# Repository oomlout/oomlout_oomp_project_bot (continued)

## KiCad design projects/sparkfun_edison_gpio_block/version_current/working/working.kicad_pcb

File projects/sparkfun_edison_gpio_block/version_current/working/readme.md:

# Edison_GPIO_Block by sparkfun  
This is a harvested standardized copy of a project from github.  
The original project can be found at:  
https://github.com/sparkfun/Edison_GPIO_Block  
Please consult that link for additional, details, files, and license information.  
Note: It was auto harvested and if the original repo had more than one board file or anything out of the ordinary the files here are likely not representative.

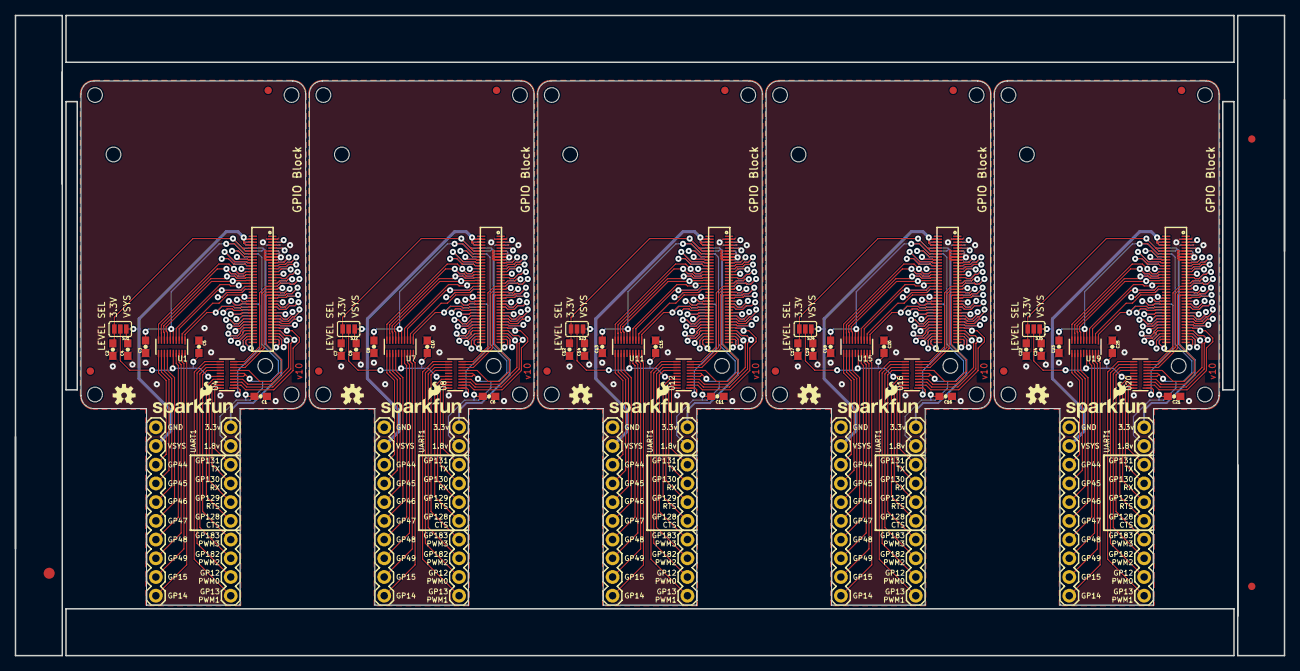
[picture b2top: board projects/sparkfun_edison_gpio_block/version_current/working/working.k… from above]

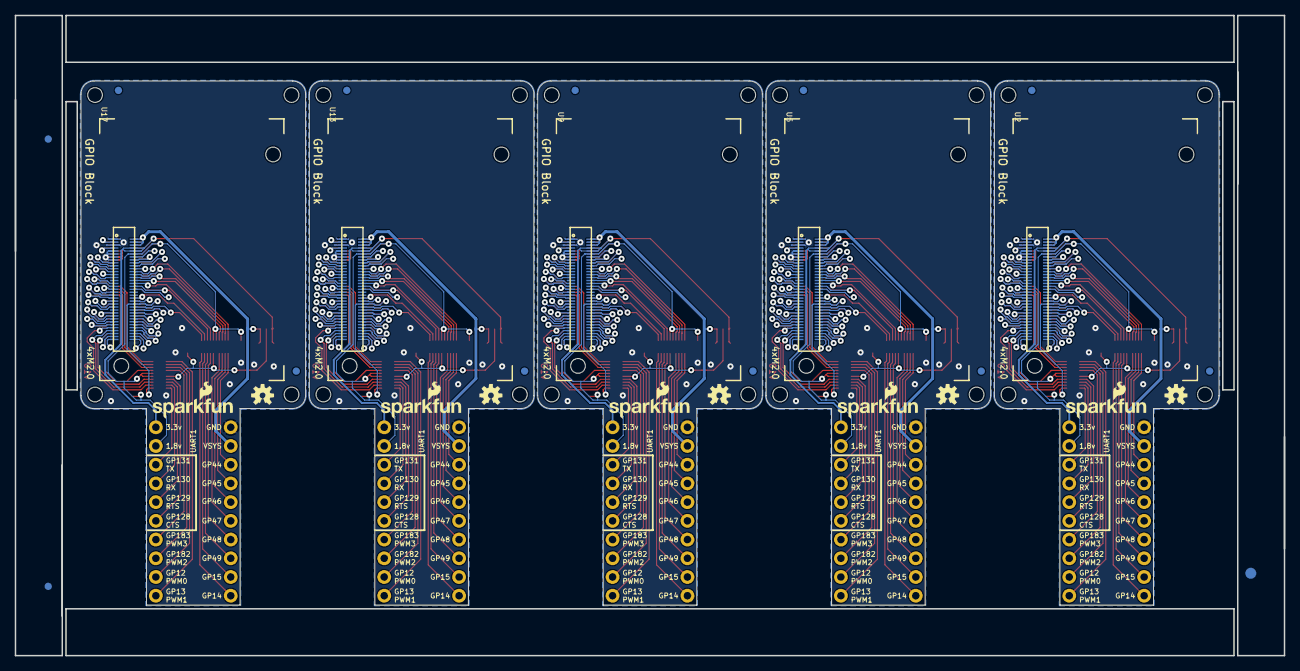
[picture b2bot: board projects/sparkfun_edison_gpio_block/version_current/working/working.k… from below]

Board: 4 copper layers, 172.2 x 86.9 mm, 126 parts (33 on the bottom side), 375 nets.

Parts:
@HOLE0, @HOLE1, @HOLE2, @HOLE3, @HOLE4, @HOLE5, @HOLE6, @HOLE7, @HOLE8, @HOLE9, @HOLE10, @HOLE11, @HOLE12, @HOLE13, @HOLE14, @HOLE15, @HOLE16, @HOLE17, @HOLE18, @HOLE19: (no value)
C1, C2, C3, C4, C5, C6, C7, C8, C9, C10, C11, C12, C13, C14, C15, C16, C17, C18, C19, C20, C21, C22, C23, C24, C25: 0.1uF; 0603-CAP
E$1, E$2: FIDUCIAL-1.5X3
E$3, E$4, E$5, E$6: FIDUCIAL-1X2
FID1, FID2, FID3, FID4, FID5, FID6, FID7, FID8, FID9, FID10, FID11, FID12, FID13, FID14, FID15, FID16, FID17, FID18, FID19, FID20: FIDUCIAL1X2; FIDUCIAL-1X2
JP1, JP2, JP3, JP4, JP5, JP6, JP7, JP8, JP9, JP10: M10"; 1X10
LOGO1, LOGO2, LOGO5, LOGO7, LOGO9, LOGO11, LOGO13, LOGO15, LOGO17, LOGO19: OSHW-LOGOS; OSHW-LOGO-S
LOGO3, LOGO4, LOGO6, LOGO8, LOGO10, LOGO12, LOGO14, LOGO16, LOGO18, LOGO20: SFE_LOGO_NAME_FLAME.1_INCH; SFE_LOGO_NAME_FLAME_.1
SJ1, SJ2, SJ3, SJ4, SJ5: GPIO Reference Select; PAD-JUMPER-3-2OF3_NC_BY_PASTE_YES_SILK_FULL_BOX
U1, U4, U7, U8, U11, U12, U15, U16, U19, U20: TXB0108; UFDFN-20
U2, U5, U9, U13, U17: EDISON_CONNECTOR_FULLMOUNTING_HOLES; EDISON_DAUGHTER
U3, U6, U10, U14, U18: EDISON_CONNECTOR_FULLHEADER; DF40C-70DP-0.4(51)

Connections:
1.8V: C1.2, C3.2, JP1.9, U1.5, U1.6, U2.12, U3.12, U4.5, U4.6
1.8V1: C6.2, C8.2, JP3.9, U5.12, U6.12, U7.5, U7.6, U8.5, U8.6
1.8V2: C11.2, C13.2, JP5.9, U9.12, U10.12, U11.5, U11.6, U12.5, U12.6
1.8V3: C16.2, C18.2, JP7.9, U13.12, U14.12, U15.5, U15.6, U16.5, U16.6
1.8V4: C21.2, C23.2, JP9.9, U17.12, U18.12, U19.5, U19.6, U20.5, U20.6
3.3V: C2.2, JP1.10, SJ1.3, U2.8, U2.10, U3.8, U3.10
3.3V1: C7.2, JP3.10, SJ2.3, U5.8, U5.10, U6.8, U6.10
3.3V2: C12.2, JP5.10, SJ3.3, U9.8, U9.10, U10.8, U10.10
3.3V3: C17.2, JP7.10, SJ4.3, U13.8, U13.10, U14.8, U14.10
3.3V4: C22.2, JP9.10, SJ5.3, U17.8, U17.10, U18.8, U18.10
DCIN: U2.14, U3.14
DCIN1: U5.14, U6.14
DCIN2: U9.14, U10.14
DCIN3: U13.14, U14.14
DCIN4: U17.14, U18.14
FAULT: U2.19, U3.19
FAULT1: U5.19, U6.19
FAULT2: U9.19, U10.19
FAULT3: U13.19, U14.19
FAULT4: U17.19, U18.19
FW_RCVR: U2.69, U3.69
FW_RCVR1: U5.69, U6.69
FW_RCVR2: U9.69, U10.69
FW_RCVR3: U13.69, U14.69
FW_RCVR4: U17.69, U18.69
GND: C1.1, C2.1, C3.1, C4.1, C5.1, JP2.10, U1.15, U2.1, U2.5, U2.9, U2.11, U2.13, U2.15, U3.1, U3.5, U3.9, U3.11, U3.13, U3.15, U4.15
GND1: C6.1, C7.1, C8.1, C9.1, C10.1, JP4.10, U5.1, U5.5, U5.9, U5.11, U5.13, U5.15, U6.1, U6.5, U6.9, U6.11, U6.13, U6.15, U7.15, U8.15
GND2: C11.1, C12.1, C13.1, C14.1, C15.1, JP6.10, U9.1, U9.5, U9.9, U9.11, U9.13, U9.15, U10.1, U10.5, U10.9, U10.11, U10.13, U10.15, U11.15, U12.15
GND3: C16.1, C17.1, C18.1, C19.1, C20.1, JP8.10, U13.1, U13.5, U13.9, U13.11, U13.13, U13.15, U14.1, U14.5, U14.9, U14.11, U14.13, U14.15, U15.15, U16.15
GND4: C21.1, C22.1, C23.1, C24.1, C25.1, JP10.10, U17.1, U17.5, U17.9, U17.11, U17.13, U17.15, U18.1, U18.5, U18.9, U18.11, U18.13, U18.15, U19.15, U20.15
GP1: U5.48, U6.48, U7.1
GP2: U5.42, U6.42, U7.2
GP3: U5.34, U6.34, U7.3
GP4: U5.32, U6.32, U7.4
GP5: U5.30, U6.30, U7.7
GP6: U5.28, U6.28, U7.8
GP7: U5.26, U6.26, U7.9
GP8: U5.25, U6.25
GP9: U5.24, U6.24, U7.10
GP10: U9.48, U10.48, U11.1
GP11: U9.42, U10.42, U11.2
GP12: U9.34, U10.34, U11.3
GP12_PWM0: U2.35, U3.35, U4.9
GP12_PWM1: U5.35, U6.35, U8.9
GP12_PWM2: U9.35, U10.35, U12.9
GP12_PWM3: U13.35, U14.35, U16.9
GP12_PWM4: U17.35, U18.35, U20.9
GP13: U9.32, U10.32, U11.4
GP13_PWM1: U2.33, U3.33, U4.10
GP13_PWM2: U5.33, U6.33, U8.10
GP13_PWM3: U9.33, U10.33, U12.10
GP13_PWM4: U13.33, U14.33, U16.10
GP13_PWM5: U17.33, U18.33, U20.10
GP14: U1.1, U2.48, U3.48
GP15: U1.2, U2.42, U3.42
GP16: U9.30, U10.30, U11.7
GP17: U9.28, U10.28, U11.8
GP18: U9.26, U10.26, U11.9
GP19: U9.25, U10.25
GP19_I2C_1_SCL: U2.41, U3.41
GP19_I2C_1_SCL1: U5.41, U6.41
GP19_I2C_1_SCL2: U9.41, U10.41
GP19_I2C_1_SCL3: U13.41, U14.41
GP19_I2C_1_SCL4: U17.41, U18.41
GP20: U9.24, U10.24, U11.10
GP20_I2C_1_SDA: U2.43, U3.43
GP20_I2C_1_SDA1: U5.43, U6.43
GP20_I2C_1_SDA2: U9.43, U10.43
GP20_I2C_1_SDA3: U13.43, U14.43
GP20_I2C_1_SDA4: U17.43, U18.43
GP21: U13.48, U14.48, U15.1
GP22: U13.42, U14.42, U15.2
GP23: U13.34, U14.34, U15.3
GP24: U13.32, U14.32, U15.4
GP25: U13.30, U14.30, U15.7
GP26: U13.28, U14.28, U15.8
GP27: U13.26, U14.26, U15.9
GP27_I2C_6_SCL: U2.45, U3.45
GP27_I2C_6_SCL1: U5.45, U6.45
GP27_I2C_6_SCL2: U9.45, U10.45
GP27_I2C_6_SCL3: U13.45, U14.45
GP27_I2C_6_SCL4: U17.45, U18.45
GP28: U13.25, U14.25
GP28_I2C_6_SDA: U2.47, U3.47
GP28_I2C_6_SDA1: U5.47, U6.47
GP28_I2C_6_SDA2: U9.47, U10.47
GP28_I2C_6_SDA3: U13.47, U14.47
GP28_I2C_6_SDA4: U17.47, U18.47
GP29: U13.24, U14.24, U15.10
GP30: U17.48, U18.48, U19.1
GP31: U17.42, U18.42, U19.2
GP32: U17.34, U18.34, U19.3
GP33: U17.32, U18.32, U19.4
GP34: U17.30, U18.30, U19.7
GP35: U17.28, U18.28, U19.8
GP36: U17.26, U18.26, U19.9
GP37: U17.25, U18.25
GP38: U17.24, U18.24, U19.10
GP40_I2S_2_CLK: U2.52, U3.52
GP40_I2S_2_CLK1: U5.52, U6.52
GP40_I2S_2_CLK2: U9.52, U10.52
GP40_I2S_2_CLK3: U13.52, U14.52
GP40_I2S_2_CLK4: U17.52, U18.52
GP41_I2S_2_FS: U2.54, U3.54
GP41_I2S_2_FS1: U5.54, U6.54
GP41_I2S_2_FS2: U9.54, U10.54
GP41_I2S_2_FS3: U13.54, U14.54
GP41_I2S_2_FS4: U17.54, U18.54
GP42_I2S_2_RXD: U2.50, U3.50
GP42_I2S_2_RXD1: U5.50, U6.50
GP42_I2S_2_RXD2: U9.50, U10.50
GP42_I2S_2_RXD3: U13.50, U14.50
GP42_I2S_2_RXD4: U17.50, U18.50
GP43_I2S_2_TXD: U2.56, U3.56
GP43_I2S_2_TXD1: U5.56, U6.56
GP43_I2S_2_TXD2: U9.56, U10.56
GP43_I2S_2_TXD3: U13.56, U14.56
GP43_I2S_2_TXD4: U17.56, U18.56
GP44: U1.10, U2.24, U3.24
GP45: U1.9, U2.26, U3.26
GP46: U1.8, U2.28, U3.28
GP47: U1.7, U2.30, U3.30
GP48: U1.4, U2.32, U3.32
GP49: U1.3, U2.34, U3.34
GP77_SD_0_CD#: U2.60, U3.60
GP77_SD_0_CD#1: U5.60, U6.60
GP77_SD_0_CD#2: U9.60, U10.60
GP77_SD_0_CD#3: U13.60, U14.60
GP77_SD_0_CD#4: U17.60, U18.60
GP78_SD_0_CLK: U2.58, U3.58
GP78_SD_0_CLK1: U5.58, U6.58
GP78_SD_0_CLK2: U9.58, U10.58
GP78_SD_0_CLK3: U13.58, U14.58
GP78_SD_0_CLK4: U17.58, U18.58
GP79_SD_0_CMD: U2.62, U3.62
GP79_SD_0_CMD1: U5.62, U6.62
GP79_SD_0_CMD2: U9.62, U10.62
GP79_SD_0_CMD3: U13.62, U14.62
GP79_SD_0_CMD4: U17.62, U18.62
GP80_SD_0_DAT0: U2.66, U3.66
GP80_SD_0_DAT1: U5.66, U6.66
GP80_SD_0_DAT2: U9.66, U10.66
GP80_SD_0_DAT3: U13.66, U14.66
GP80_SD_0_DAT4: U17.66, U18.66
GP81_SD_0_DAT1: U2.70, U3.70
GP81_SD_0_DAT2: U5.70, U6.70
GP81_SD_0_DAT3: U9.70, U10.70
GP81_SD_0_DAT4: U13.70, U14.70
GP81_SD_0_DAT5: U17.70, U18.70
GP82_SD_0_DAT1: U5.64, U6.64
GP82_SD_0_DAT2: U2.64, U3.64
GP82_SD_0_DAT3: U9.64, U10.64
GP82_SD_0_DAT4: U13.64, U14.64
GP82_SD_0_DAT5: U17.64, U18.64
GP83_SD_0_DAT1: U5.68, U6.68
GP83_SD_0_DAT2: U9.68, U10.68
GP83_SD_0_DAT3: U2.68, U3.68
GP83_SD_0_DAT4: U13.68, U14.68
GP83_SD_0_DAT5: U17.68, U18.68
GP84_SD_CLK_FB: U2.44, U3.44
GP84_SD_CLK_FB1: U5.44, U6.44
GP84_SD_CLK_FB2: U9.44, U10.44
GP84_SD_CLK_FB3: U13.44, U14.44
GP84_SD_CLK_FB4: U17.44, U18.44
GP109_SPI_2_CLK: U2.55, U3.55
GP109_SPI_2_CLK1: U5.55, U6.55
GP109_SPI_2_CLK2: U9.55, U10.55
GP109_SPI_2_CLK3: U13.55, U14.55
GP109_SPI_2_CLK4: U17.55, U18.55
GP110_SPI_2_FS0: U2.53, U3.53
GP110_SPI_2_FS1: U5.53, U6.53
GP110_SPI_2_FS2: U9.53, U10.53
GP110_SPI_2_FS3: U13.53, U14.53
GP110_SPI_2_FS4: U17.53, U18.53
GP111_SPI_2_FS1: U2.51, U3.51
GP111_SPI_2_FS2: U5.51, U6.51
GP111_SPI_2_FS3: U9.51, U10.51
GP111_SPI_2_FS4: U13.51, U14.51
GP111_SPI_2_FS5: U17.51, U18.51
GP114_SPI_2_RXD: U2.59, U3.59
GP114_SPI_2_RXD1: U5.59, U6.59
GP114_SPI_2_RXD2: U9.59, U10.59
GP114_SPI_2_RXD3: U13.59, U14.59
GP114_SPI_2_RXD4: U17.59, U18.59
GP115_SPI_2_TXD: U2.57, U3.57
GP115_SPI_2_TXD1: U5.57, U6.57
GP115_SPI_2_TXD2: U9.57, U10.57
GP115_SPI_2_TXD3: U13.57, U14.57
GP115_SPI_2_TXD4: U17.57, U18.57
GP128_UART_1_CTS: U2.65, U3.65, U4.4
GP128_UART_1_CTS1: U5.65, U6.65, U8.4
GP128_UART_1_CTS2: U9.65, U10.65, U12.4
GP128_UART_1_CTS3: U13.65, U14.65, U16.4
GP128_UART_1_CTS4: U17.65, U18.65, U20.4
GP129_UART_1_RTS: U2.63, U3.63, U4.3
GP129_UART_1_RTS1: U5.63, U6.63, U8.3
GP129_UART_1_RTS2: U9.63, U10.63, U12.3
GP129_UART_1_RTS3: U13.63, U14.63, U16.3
GP129_UART_1_RTS4: U17.63, U18.63, U20.3
GP130_UART_1_RX: U2.61, U3.61, U4.2
GP130_UART_1_RX1: U5.61, U6.61, U8.2
GP130_UART_1_RX2: U9.61, U10.61, U12.2
GP130_UART_1_RX3: U13.61, U14.61, U16.2
GP130_UART_1_RX4: U17.61, U18.61, U20.2
GP131_UART_1_TX: U2.46, U3.46, U4.1
GP131_UART_1_TX1: U5.46, U6.46, U8.1
GP131_UART_1_TX2: U9.46, U10.46, U12.1
GP131_UART_1_TX3: U13.46, U14.46, U16.1
GP131_UART_1_TX4: U17.46, U18.46, U20.1
GP134_UART_2_RX: U2.22, U3.22
GP134_UART_2_RX1: U5.22, U6.22
GP134_UART_2_RX2: U9.22, U10.22
GP134_UART_2_RX3: U13.22, U14.22
GP134_UART_2_RX4: U17.22, U18.22
GP135_UART_2_TX: U2.27, U3.27
GP135_UART_2_TX1: U5.27, U6.27
GP135_UART_2_TX2: U9.27, U10.27
GP135_UART_2_TX3: U13.27, U14.27
GP135_UART_2_TX4: U17.27, U18.27
GP165: U2.25, U3.25
GP182_PWM1: U5.37, U6.37, U8.8
GP182_PWM2: U2.37, U3.37, U4.8
GP182_PWM3: U9.37, U10.37, U12.8
GP182_PWM4: U13.37, U14.37, U16.8
GP182_PWM5: U17.37, U18.37, U20.8
GP183_PWM1: U5.39, U6.39, U8.7
GP183_PWM2: U9.39, U10.39, U12.7
GP183_PWM3: U2.39, U3.39, U4.7
GP183_PWM4: U13.39, U14.39, U16.7
GP183_PWM5: U17.39, U18.39, U20.7
GPIO_REFERENCE_SELECT: C5.2, SJ1.2, U1.16, U4.16
GPIO_REFERENCE_SELECT1: C10.2, SJ2.2, U7.16, U8.16
GPIO_REFERENCE_SELECT2: C15.2, SJ3.2, U11.16, U12.16
GPIO_REFERENCE_SELECT3: C20.2, SJ4.2, U15.16, U16.16
GPIO_REFERENCE_SELECT4: C25.2, SJ5.2, U19.16, U20.16
MSIC_SLP_CLK: U2.7, U3.7
MSIC_SLP_CLK1: U5.7, U6.7
MSIC_SLP_CLK2: U9.7, U10.7
MSIC_SLP_CLK3: U13.7, U14.7
MSIC_SLP_CLK4: U17.7, U18.7
unnamed: JP2.8, U1.11
unnamed: JP2.7, U1.12
unnamed: JP2.6, U1.13
unnamed: JP2.5, U1.14
unnamed: JP2.4, U1.17
unnamed: JP2.3, U1.18
unnamed: JP2.2, U1.19
unnamed: JP2.1, U1.20
unnamed: JP4.8, U7.11
unnamed: JP4.7, U7.12
unnamed: JP1.4, U4.14
unnamed: JP1.3, U4.13
unnamed: JP1.2, U4.12
unnamed: JP1.1, U4.11
unnamed: JP1.5, U4.17
unnamed: JP1.6, U4.18
unnamed: JP1.7, U4.19
unnamed: JP1.8, U4.20
unnamed: JP4.6, U7.13
unnamed: JP4.5, U7.14
unnamed: JP4.4, U7.17
unnamed: JP4.3, U7.18
unnamed: JP4.2, U7.19
unnamed: JP4.1, U7.20
unnamed: JP3.5, U8.17
unnamed: JP3.6, U8.18
unnamed: JP3.7, U8.19
unnamed: JP3.8, U8.20
unnamed: JP3.4, U8.14
unnamed: JP3.3, U8.13
unnamed: JP3.2, U8.12
unnamed: JP3.1, U8.11
unnamed: JP6.8, U11.11
unnamed: JP6.7, U11.12
unnamed: JP6.6, U11.13
unnamed: JP6.5, U11.14
unnamed: JP6.4, U11.17
unnamed: JP6.3, U11.18
unnamed: JP6.2, U11.19
unnamed: JP6.1, U11.20
unnamed: JP5.5, U12.17
unnamed: JP5.6, U12.18
unnamed: JP5.7, U12.19
unnamed: JP5.8, U12.20
unnamed: JP5.4, U12.14
unnamed: JP5.3, U12.13
unnamed: JP5.2, U12.12
unnamed: JP5.1, U12.11
unnamed: JP8.8, U15.11
unnamed: JP8.7, U15.12
unnamed: JP8.6, U15.13
unnamed: JP8.5, U15.14
unnamed: JP8.4, U15.17
unnamed: JP8.3, U15.18
unnamed: JP8.2, U15.19
unnamed: JP8.1, U15.20
unnamed: JP7.5, U16.17
unnamed: JP7.6, U16.18
unnamed: JP7.7, U16.19
unnamed: JP7.8, U16.20
unnamed: JP7.4, U16.14
unnamed: JP7.3, U16.13
unnamed: JP7.2, U16.12
unnamed: JP7.1, U16.11
unnamed: JP10.8, U19.11
unnamed: JP10.7, U19.12
unnamed: JP10.6, U19.13
unnamed: JP10.5, U19.14
unnamed: JP10.4, U19.17
unnamed: JP10.3, U19.18
unnamed: JP10.2, U19.19
unnamed: JP10.1, U19.20
unnamed: JP9.5, U20.17
unnamed: JP9.6, U20.18
unnamed: JP9.7, U20.19
unnamed: JP9.8, U20.20
unnamed: JP9.4, U20.14
unnamed: JP9.3, U20.13
unnamed: JP9.2, U20.12
unnamed: JP9.1, U20.11
OSC_CLK_OUT: U2.67, U3.67
OSC_CLK_OUT1: U5.67, U6.67
OSC_CLK_OUT2: U9.67, U10.67
OSC_CLK_OUT3: U13.67, U14.67
OSC_CLK_OUT4: U17.67, U18.67
PSW: U2.21, U3.21
PSW1: U5.21, U6.21
PSW2: U9.21, U10.21
PSW3: U13.21, U14.21
PSW4: U17.21, U18.21
PWRBTN#: U2.17, U3.17
PWRBTN#1: U5.17, U6.17
PWRBTN#2: U9.17, U10.17
PWRBTN#3: U13.17, U14.17
PWRBTN#4: U17.17, U18.17
RCVR_MODE: U2.31, U3.31
RCVR_MODE1: U5.31, U6.31
RCVR_MODE2: U9.31, U10.31
RCVR_MODE3: U13.31, U14.31
RCVR_MODE4: U17.31, U18.31
RESET_OUT#: U2.36, U3.36
RESET_OUT#1: U5.36, U6.36
RESET_OUT#2: U9.36, U10.36
RESET_OUT#3: U13.36, U14.36
RESET_OUT#4: U17.36, U18.36
USB_DN: U2.18, U3.18
USB_DN1: U5.18, U6.18
USB_DN2: U9.18, U10.18
USB_DN3: U13.18, U14.18
USB_DN4: U17.18, U18.18
USB_DP: U2.16, U3.16
USB_DP1: U5.16, U6.16
USB_DP2: U9.16, U10.16
USB_DP3: U13.16, U14.16
USB_DP4: U17.16, U18.16
USB_ID: U2.3, U3.3
USB_ID1: U5.3, U6.3
USB_ID2: U9.3, U10.3
USB_ID3: U13.3, U14.3
USB_ID4: U17.3, U18.3
USB_VBUS: U2.20, U3.20
USB_VBUS1: U5.20, U6.20
USB_VBUS2: U9.20, U10.20
USB_VBUS3: U13.20, U14.20
USB_VBUS4: U17.20, U18.20
VSYS: C4.2, JP2.9, SJ1.1, U2.2, U2.4, U2.6, U3.2, U3.4, U3.6
VSYS1: C9.2, JP4.9, SJ2.1, U5.2, U5.4, U5.6, U6.2, U6.4, U6.6
VSYS2: C14.2, JP6.9, SJ3.1, U9.2, U9.4, U9.6, U10.2, U10.4, U10.6
VSYS3: C19.2, JP8.9, SJ4.1, U13.2, U13.4, U13.6, U14.2, U14.4, U14.6
VSYS4: C24.2, JP10.9, SJ5.1, U17.2, U17.4, U17.6, U18.2, U18.4, U18.6
V_BAT_BKUP: U2.23, U3.23
V_BAT_BKUP1: U5.23, U6.23
V_BAT_BKUP2: U9.23, U10.23
V_BAT_BKUP3: U13.23, U14.23
V_BAT_BKUP4: U17.23, U18.23

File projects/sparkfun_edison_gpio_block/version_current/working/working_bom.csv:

"Id";"Designator";"Footprint";"Quantity";"Designation";"Supplier and ref";
1;"U4,U8,U12,U20,U19,U11,U15,U7,U1,U16";"UFDFN-20";10;"TXB0108";;;
2;"C16,C21,C23,C8,C17,C22,C18,C10,C12,C6,C2,C20,C1,C14,C7,C3,C19,C13,C9,C4,C24,C15,C25,C5,C11";"0603-CAP";25;"0.1uF";;;
3;"SJ4,SJ5,SJ3,SJ1,SJ2";"PAD-JUMPER-3-2OF3_NC_BY_PASTE_YES_SILK_FULL_BOX";5;"GPIO Reference Select";;;
4;"JP7,JP10,JP9,JP3,JP1,JP4,JP2,JP5,JP6,JP8";"1X10";10;"M10"";;;
5;"LOGO20,LOGO4,LOGO12,LOGO8,LOGO16,LOGO6,LOGO14,LOGO18,LOGO3,LOGO10";"SFE_LOGO_NAME_FLAME_.1";10;"SFE_LOGO_NAME_FLAME.1_INCH";;;
6;"@HOLE17,@HOLE11,@HOLE16,@HOLE13,@HOLE2,@HOLE15,@HOLE9,@HOLE7,@HOLE19,@HOLE12,@HOLE5,@HOLE14,@HOLE0,@HOLE18,@HOLE10,@HOLE6,@HOLE8,@HOLE4,@HOLE3,@HOLE1";"";20;"";;;
7;"FID9,FID6,FID5,FID13,FID18,FID17,FID10,FID1,FID14,FID2,FID19,FID15,FID7,FID3,FID20,FID16,FID11,FID4,FID12,FID8";"FIDUCIAL-1X2";20;"FIDUCIAL1X2";;;
8;"LOGO19,LOGO1,LOGO11,LOGO7,LOGO15,LOGO17,LOGO2,LOGO9,LOGO13,LOGO5";"OSHW-LOGO-S";10;"OSHW-LOGOS";;;
9;"E$5,E$4,E$6,E$3";"FIDUCIAL-1X2";4;"";;;
10;"E$1,E$2";"FIDUCIAL-1.5X3";2;"";;;
11;"U14,U18,U10,U3,U6";"DF40C-70DP-0.4(51)";5;"EDISON_CONNECTOR_FULLHEADER";;;
12;"U9,U13,U2,U5,U17";"EDISON_DAUGHTER";5;"EDISON_CONNECTOR_FULLMOUNTING_HOLES";;;
